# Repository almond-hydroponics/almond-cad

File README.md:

View this project on [CADLAB.io](https://cadlab.io/project/24117). 

# almond-cad
Repository for hydroponics hardware cad design

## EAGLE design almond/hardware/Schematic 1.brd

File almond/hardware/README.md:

# description
The Eagle CAD project must be created in this folder. Going by this standard, you team members will know instantly where the schematics and board designs are and start working.

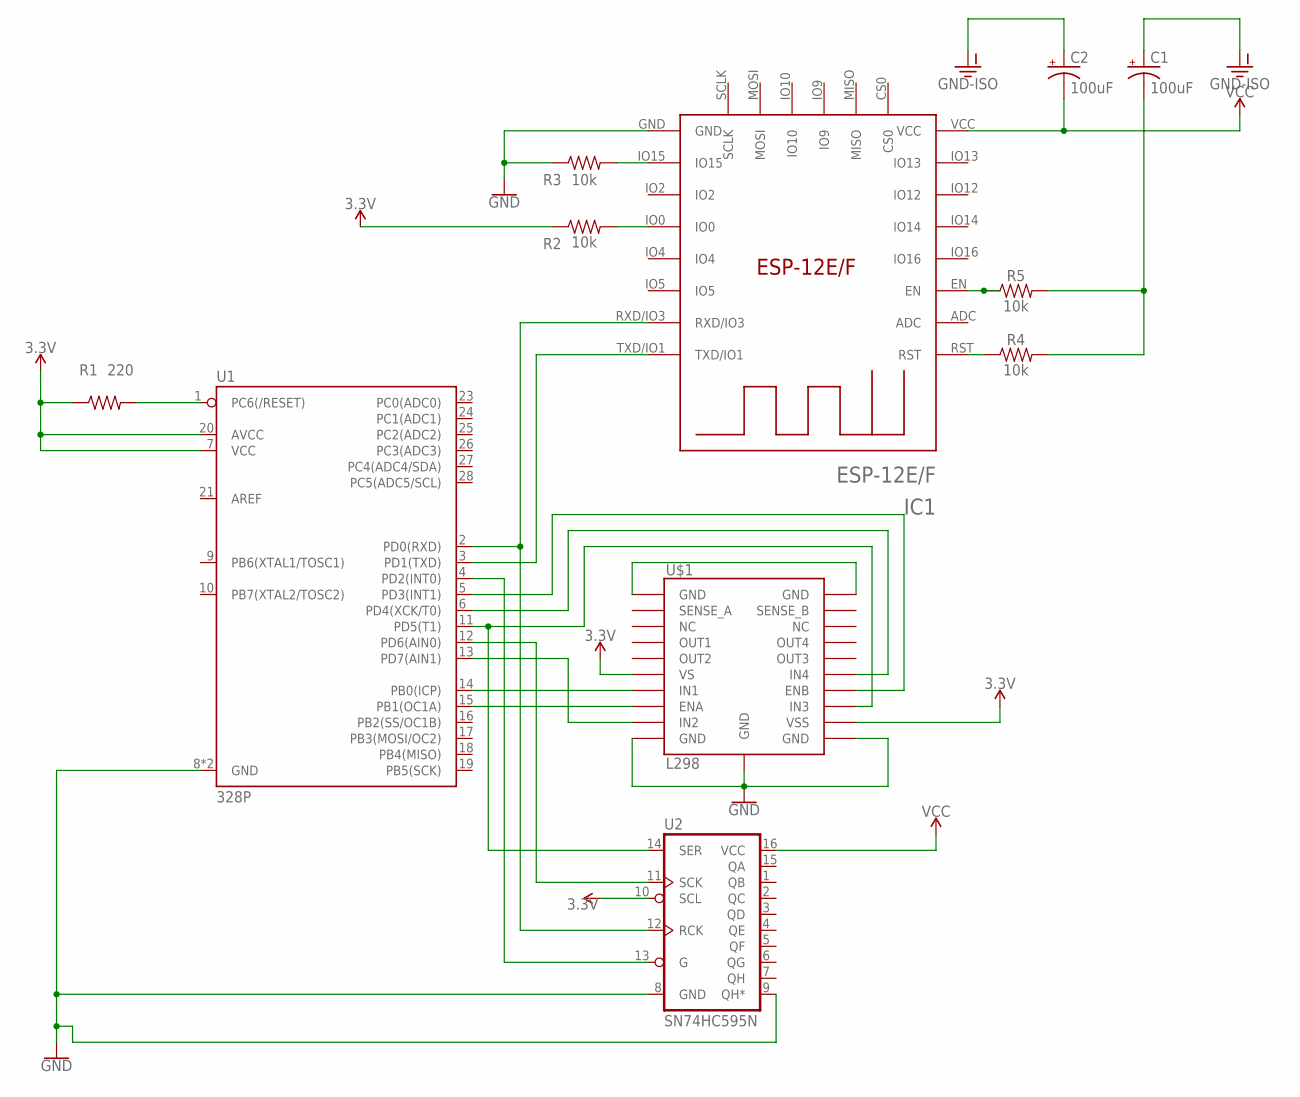
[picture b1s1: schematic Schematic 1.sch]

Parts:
C1, C2: 100uF; CPOL-RADIAL-2.5MM-6.5MM
IC1: ESP-12E/F; ESP-12E
R1: 220; 0603
R2, R3, R4, R5: 10k; AXIAL-0.3
U1: 328P; DIP28
U2: SN74HC595N; DIP16
U$1: L298; POWERSO20_L298_PAD

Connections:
3.3V: R1.1, R2.P$1 (1), U1.7 (VCC), U1.20 (AVCC), U2.10 (SCL), U$1.6 (VS), U$1.12 (VSS)
GND: IC1.GND, R3.P$1 (1), U1.8 (GND), U1.22 (GND), U2.8 (GND), U2.9 (QH*), U$1.10 (GND), U$1.11 (GND), U$1.PAD (GND)
GND-ISO: C1.1 (+), C2.1 (+)
unnamed: R1.2, U1.1 (PC6(/RESET))
unnamed: U1.13 (PD7(AIN1)), U$1.9 (IN2)
unnamed: IC1.TXD/IO1, U1.3 (PD1(TXD))
unnamed: U1.5 (PD3(INT1)), U$1.14 (ENB)
unnamed: U1.11 (PD5(T1)), U2.14 (SER), U$1.13 (IN3)
unnamed: U$1.1 (GND), U$1.20 (GND)
unnamed: U1.14 (PB0(ICP)), U$1.7 (IN1)
unnamed: U1.15 (PB1(OC1A)), U$1.8 (ENA)
unnamed: U1.4 (PD2(INT0)), U2.13 (G)
unnamed: U1.6 (PD4(XCK/T0)), U$1.15 (IN4)
unnamed: IC1.RXD/IO3, U1.2 (PD0(RXD)), U2.12 (RCK)
unnamed: U1.12 (PD6(AIN0)), U2.11 (SCK)
unnamed: IC1.IO0, R2.P$2 (2)
unnamed: IC1.IO15, R3.P$2 (2)
unnamed: C1.2 (-), R4.P$2 (2), R5.P$2 (2)
unnamed: IC1.EN, R5.P$1 (1)
unnamed: IC1.RST, R4.P$1 (1)
VCC: C2.2 (-), IC1.VCC, U2.16 (VCC)

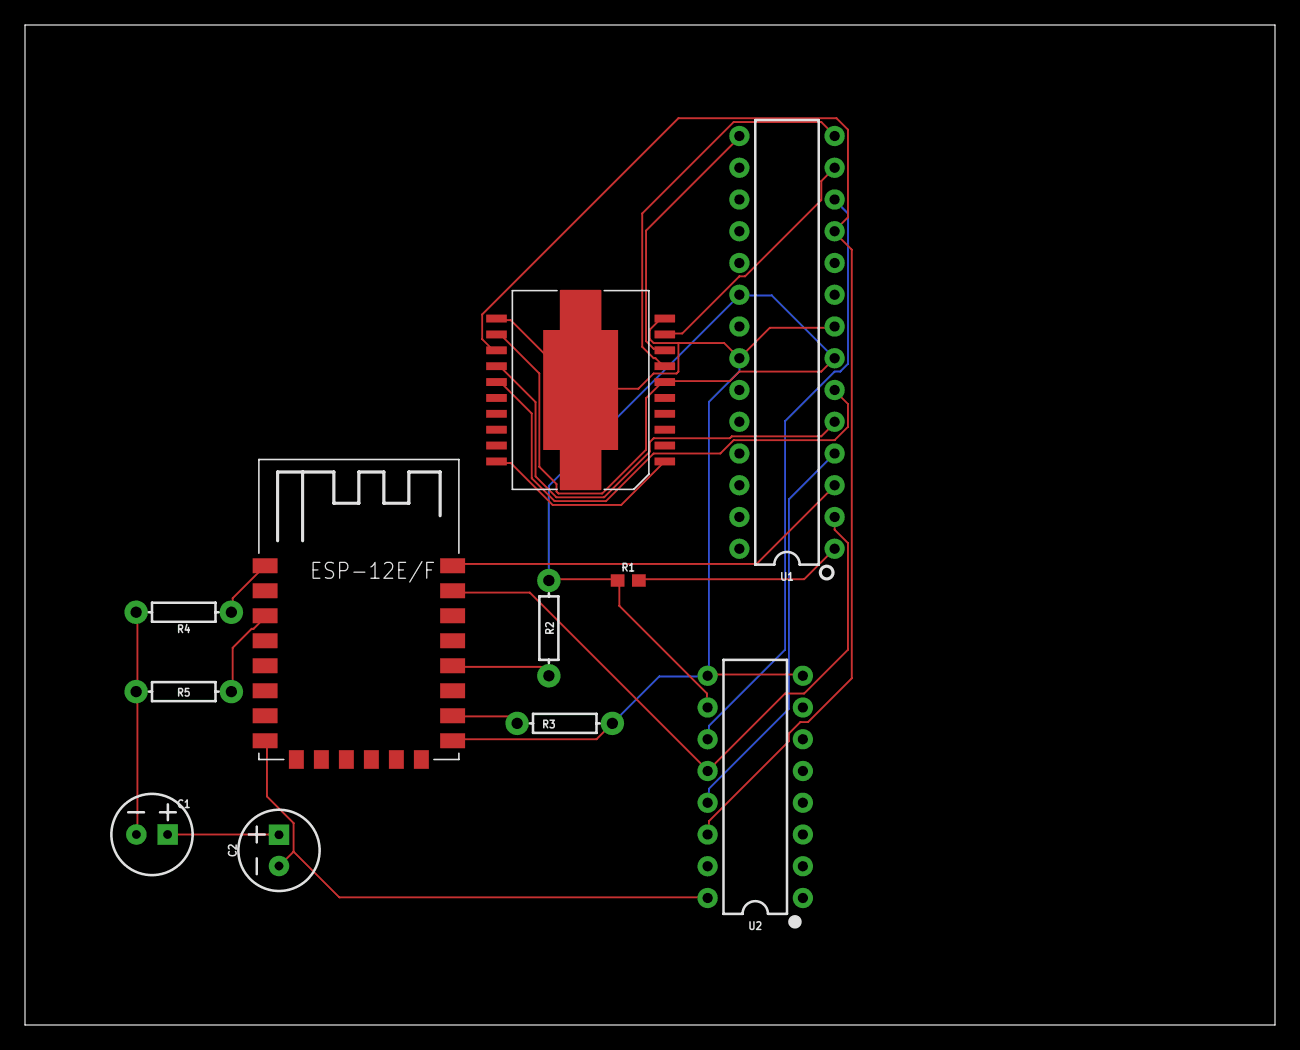
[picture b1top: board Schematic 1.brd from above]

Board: 2 copper layers, 100.0 x 80.0 mm, 11 parts (0 on the bottom side), 21 nets.

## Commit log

2021-04-01 Backlink to CADLAB.io has been added.
2021-04-01 feat: add main board to project
2021-04-01 feat: add project structure
2021-04-20 feat: change configuration
2021-04-22 feat:add new changes
2021-04-22 feat: added schematic and board

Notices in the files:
parts and their libraries:
SparkFun-Capacitors: Licensing: Creative Commons ShareAlike 4.0 International - https://creativecommons.org/licenses/by-sa/4.0
